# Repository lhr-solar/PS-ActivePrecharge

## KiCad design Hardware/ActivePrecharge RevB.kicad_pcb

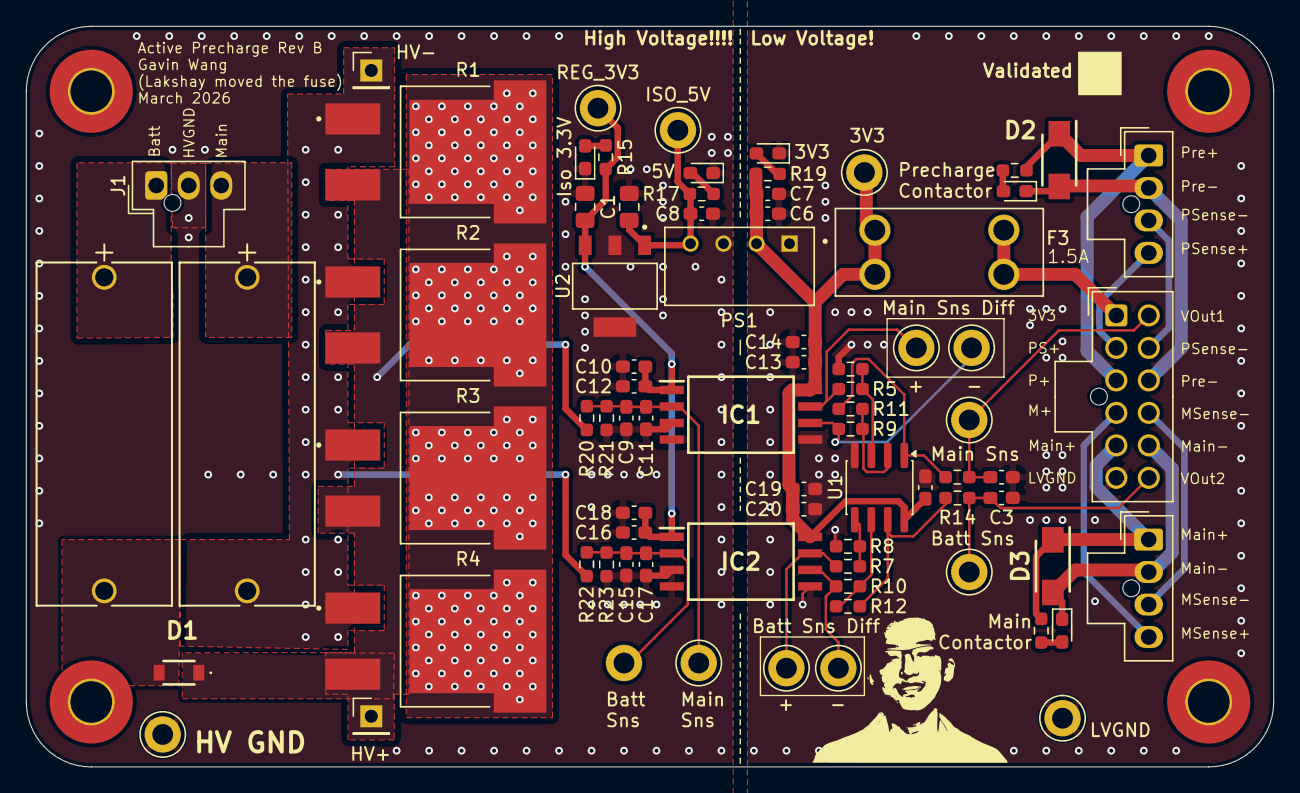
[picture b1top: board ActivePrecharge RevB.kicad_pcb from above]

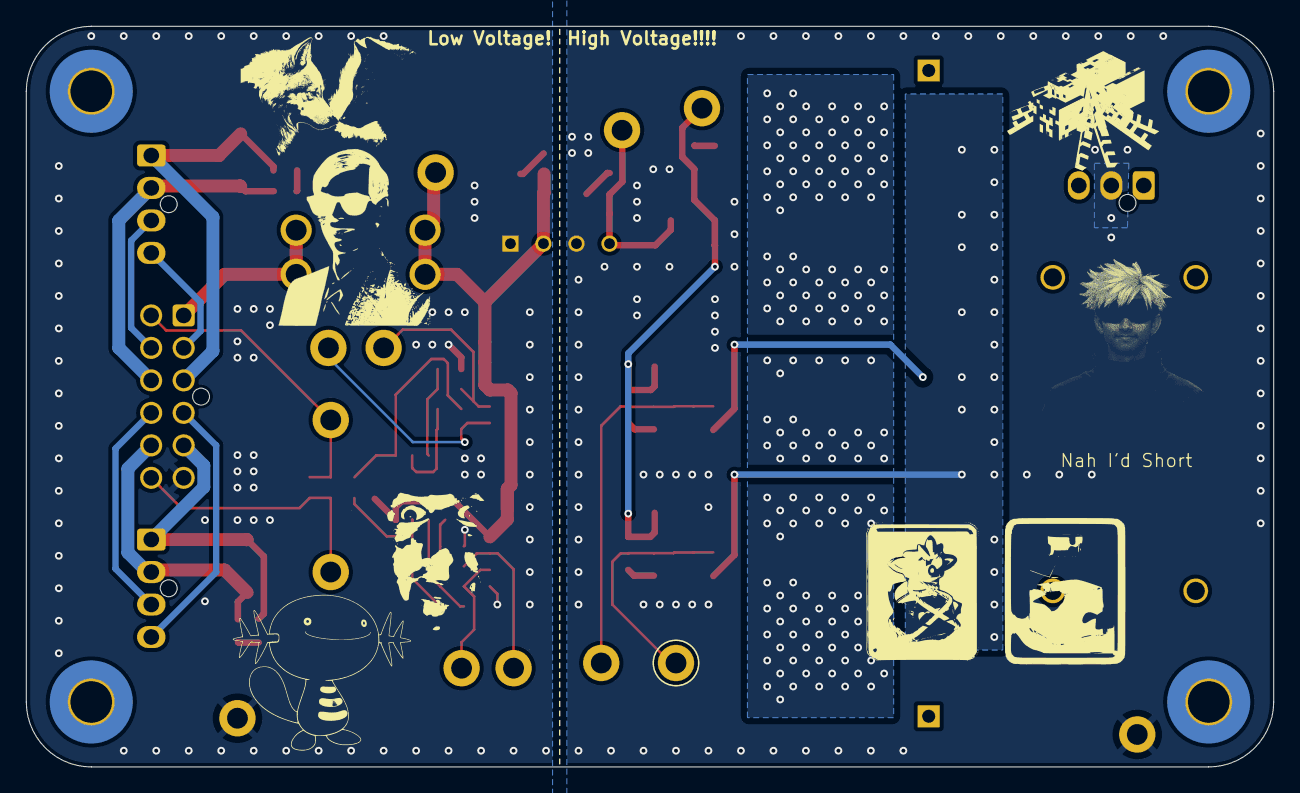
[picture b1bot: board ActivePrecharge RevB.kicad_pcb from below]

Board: 2 copper layers, 96.0 x 57.0 mm, 84 parts (2 on the bottom side), 39 nets.

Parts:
C1, C4: 10uF; C_0805_2012Metric_Pad1.18x1.45mm_HandSolder
C2, C3: 10nF; C_0603_1608Metric_Pad1.08x0.95mm_HandSolder
C5, C6, C7, C8, C9, C12, C13, C15, C18, C19: 1uF; C_0603_1608Metric_Pad1.08x0.95mm_HandSolder
C10, C14, C16, C20: 100nF; C_0603_1608Metric_Pad1.08x0.95mm_HandSolder
C11, C17: 1nF; C_0603_1608Metric_Pad1.08x0.95mm_HandSolder
D1: RSX068MP2STR
D2, D3: VSSAF522-M3/H; SODFL5026X125N
D4, D5, D6, D7, D8: LED; LED_0603_1608Metric_Pad1.05x0.95mm_HandSolder
F1, F2: 1.5A; HV-Fuse
F3: 1.5A; FUSE_3568
H1, H2, H3, H4: MountingHole_Pad; MountingHole_3.2mm_M3_Pad_TopBottom
IC1, IC2: AMC1350DWVR; SOIC127P1150X280-8N
J1: HVConnector; Molex_Nano-Fit_105309-xx03_1x03_P2.50mm_Vertical
J2: PrechargeContactor; Molex_Nano-Fit_105309-xx04_1x04_P2.50mm_Vertical
J3: MainContactor; Molex_Nano-Fit_105309-xx04_1x04_P2.50mm_Vertical
J4: ExportConnector; Molex_Nano-Fit_105310-xx12_2x06_P2.50mm_Vertical
J5: HV+; PinHeader_1x01_P2.54mm_Vertical
J6: HV-; PinHeader_1x01_P2.54mm_Vertical
LOGO1: Dr. Hallock; Hallock_Image_Tiny
LOGO2: Dr. Hallock; LHRs_LOGO
PS1: RM-3.305S; CONV_RM-3.305S
R1, R2, R3, R4: 330; RES_PWR263S-35-3300F
R5, R6, R7, R8, R9, R10, R11, R12, R16, R18: 10k; R_0603_1608Metric_Pad0.98x0.95mm_HandSolder
R13, R14: 10; R_0603_1608Metric_Pad0.98x0.95mm_HandSolder
R15, R17, R19: 1k; R_0603_1608Metric_Pad0.98x0.95mm_HandSolder
R20, R22: 100k; R_0603_1608Metric_Pad0.98x0.95mm_HandSolder
R21, R23: 2.49k; R_0603_1608Metric_Pad0.98x0.95mm_HandSolder
TP1: HVGND; TestPoint_Keystone_5005-5009_Compact
TP2: VOut1; TestPoint_Keystone_5005-5009_Compact
TP3: VOut2; TestPoint_Keystone_5005-5009_Compact
TP4: REG_3V3; TestPoint_Keystone_5005-5009_Compact
TP5: ISO_5V; TestPoint_Keystone_5005-5009_Compact
TP6, TP9: Vin; TestPoint_Keystone_5005-5009_Compact
TP7, TP10: V+; TestPoint_Keystone_5005-5009_Compact
TP8, TP11: V-; TestPoint_Keystone_5005-5009_Compact
TP12: 3v3; TestPoint_Keystone_5005-5009_Compact
TP13: GND; TestPoint_Keystone_5005-5009_Compact
U1: TLV9002QDRQ1; SOIC-8_3.9x4.9mm_P1.27mm
U2: LT1963AEST-3.3#TRPBF; VREG_LT1963AEST-3.3_TRPBF

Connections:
3V3: C5.1, C6.1, C7.1, C13.1, C14.1, C19.1, C20.1, F3.1, IC1.8 (VDD2), IC2.8 (VDD2), PS1.2 (+VIN), R19.1, TP12.1, U1.8 (V+)
/3V3_PreFuse: F3.2, J4.1
/HEAT_DISSIPATION: R1.3, R2.3, R3.3, R4.3
/HV+_Fused: D1.2 (A), F1.2
/HV+_PreFuse: F1.1, J1.1
/HV-_PreFuse: F2.1, J1.3
/Main+: D3.1 (K), J3.1 (Con+(24V)), J4.5, R18.1
/Main-: D3.2 (A), D7.1 (K), J3.2 (Con-), J4.11
/MainSense+: J3.4 (Sense+(24V)), J4.4
/MainSense-: J3.3 (Sense-), J4.10
/Pre+: D2.1 (K), J2.1 (Con+(24V)), J4.3, R16.1
/Pre-: D2.2 (A), D5.1 (K), J2.2 (Con-), J4.9
/PreSense+: J2.4 (Sense+(24V)), J4.2
/PreSense-: J2.3 (Sense-), J4.8
/V1+: IC1.7 (OUTP), R5.2, TP7.1
/V1-: IC1.6 (OUTN), R9.2, TP8.1
/V2+: IC2.7 (OUTP), R7.2, TP10.1
/V2-: IC2.6 (OUTN), R10.1, TP11.1
/VOut1: C2.1, J4.7, R13.1, TP2.1
/VOut2: C3.1, J4.12, R14.1, TP3.1
/Vin1: C9.1, C11.1, IC1.2 (INP), R20.1, R21.2, TP6.1
/Vin2: C15.1, C17.1, IC2.2 (INP), R22.1, R23.2, TP9.1
HV+: D1.1 (K), J5.1, R1.2, R2.2, R3.2, R4.2, R20.2
HV-: F2.2, J6.1, R1.1, R2.1, R3.1, R4.1, R22.2
HVGND: C1.2, C4.1, C8.1, C9.2, C10.2, C11.2, C12.2, C15.2, C16.2, C17.2, C18.2, D4.1 (K), D6.1 (K), IC1.3 (INN), IC1.4 (GND1), IC2.3 (INN), IC2.4 (GND1), J1.2, PS1.3 (-VOUT), R21.1, R23.1, TP1.1, U2.2 (GND), U2.4 (TAB)
ISO_5V: C1.1, C8.2, PS1.4 (+VOUT), R17.1, TP5.1, U2.1 (IN)
LVGND: C2.2, C3.2, C5.2, C6.2, C7.2, C13.2, C14.2, C19.2, C20.2, D8.1 (K), IC1.5 (GND2), IC2.5 (GND2), J4.6, PS1.1 (-VIN), R6.1, R8.1, TP13.1, U1.4 (V-)
unnamed: D4.2 (A), R15.2
unnamed: D5.2 (A), R16.2
unnamed: D6.2 (A), R17.2
unnamed: D7.2 (A), R18.2
unnamed: D8.2 (A), R19.2
unnamed: R11.1, R13.2, U1.1
unnamed: R12.2, R14.2, U1.7
unnamed: R5.1, R6.2, U1.3 (+)
unnamed: R9.1, R11.2, U1.2 (-)
unnamed: R7.1, R8.2, U1.5 (+)
unnamed: R10.2, R12.1, U1.6 (-)
REG_3V3: C4.2, C10.1, C12.1, C16.1, C18.1, IC1.1 (VDD1), IC2.1 (VDD1), R15.1, TP4.1, U2.3 (OUT)

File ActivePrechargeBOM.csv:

Qty,Value,P/N,Description
1,TLV9002QDRQ1,TLV9002QDRQ1,
3,1k,CRCW06031K00FKEI ,1k Resistor
2,1nF,MLASU063SB7102KFNA01,1nF Capacitor
10,1uF,MLASU168SB5105KTNA01,1uF Capacitors
3,1.5A,3568,1.5A Fuse
2,2.49k,CRCW06032K49FKEAC,2.49k Resistor
2,10,CRCW060310R0FKEE,10 Ohm Resistor
10,10k,CRCW060310K0FKEI,10k Resistor
2,10nF,MSASH168SB5103KTNA01,10nF Capacitor
2,10uF,GRM21BR61H106KE43K,10uF Capacitor
2,100k,CRCW0603100KFKEE,100k Resistor
4,100nF,MLASH168SB7104KTNA01,100nF Capacitor
1,RM-3.305S, RM-3.305S,3.3V to 5V DC/DC
1,LT1963AEST-3.3#TRPBF,LT1963AEST-3.3#TRPBF ,"3.3V, 1.5A, Low Noise, Fast Transient Response LDO Regulator, SOT-223"
2,VSSAF522-M3/H,VSSAF522-M3/H,Flyback diode
1,ExportConnector,1053101112,"Generic connector, double row, 02x06, counter clockwise pin numbering scheme (similar to DIP package numbering), script generated (kicad-library-utils/schlib/autogen/connector/)"
2,Conn_01x01_Pin,,"Generic connector, single row, 01x01, script generated"
1,Conn_01x02_Pin,,"Generic connector, single row, 01x02, script generated"
1,HVConnector,1053091103,"Generic connector, single row, 01x03, script generated (kicad-library-utils/schlib/autogen/connector/)"
2,AMC1350DWVR,AMC1350DWVR,Iso Opamps
5,LED,XL-1608UBC-06A,Light emitting diode
1,PrechargeContactor,1053091104,Pinout for contactor connectors.
1,MainContactor,1053091104,Pinout for contactor connectors.
3,330,  PWR263S-35-3300F,Precharge Resistor
1,330,  PWR263S-35-3300F,Precharge Resistor
1,RSX068MP2STR,RSX068MP2STR,Schottky diode

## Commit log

2025-09-22 Active Precharge Rev A
2025-09-23 Active Precharge Rev A with LDO and 3.3-5 ISO
2025-09-26 Active Precharge Rev A with comments addressed
2025-09-26 Active Precharge Rev A after Tony review
2025-09-27 With Ravi comments
2025-09-27 With footprints assigned
2025-09-30 Lakshay's comments addressed
2025-10-02 Lakshay's comments addressed, still need to move to new branch
2025-10-02 A few minor changes added bc i forgot some stuff
2025-10-03 Last changes addressed with organization changes and the new resolution implementation
2025-10-03 Adjustments made after Changxu examined the opamp circuit
2025-10-03 Added math for tolerancing on last opamp
2025-10-04 First Initial PCB Layout Finished
2025-10-11 All layout changes made except new symbol for precharge resistors for heat dissipation and new fuses
2025-10-11 All new comments addressed
2025-10-11 LVGND Stitching vias added to edges
2025-10-11 Part Numbers fleshed out
2025-10-11 Implemented all changes
2025-10-11 Renamed connector pins and added stitching vias for LVGND island
2025-10-11 Fixed pin, LED, and connector names being overwritten after updating PCB
2025-10-11 Deleted a redundant via on a thermal pad
2025-10-14 After nuking
2025-10-25 BOM generated
2025-10-25 BOM is actually inside the directory now
2025-11-08 Fixed 0.8V reference circuit short on accidental node for divider side
2025-12-19 Removed the 0.8V Reference circuit, changed the opamp, and changed the testpoints to make testing easier. Not sure how the connector is meant to be set up though
2025-12-26 Changed opamp to the TLV9002QDRQ1, separated the pin test points, changed 24V LED resitors to 10k (I don't remember what resistance you guys said), made 2 hierarchical sheets that are linked copies, 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
2025-12-27 Did some of the initial layout after schematic changes, concerned about the choking on how i currently have the opamp kind of set up, also havent touched the testpoints yet so that will probably make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
2026-01-02 First draft of the layout is complete, I think its workable rn but the vias might need a little work
2026-01-03 Addressed most things, still need to add more stitching vias, flybacks, change testpoints, and compact everything some more
2026-01-04 Made all layout changes. Ready for review. Also deleted some unnecessary files to clean up the libraries.
2026-01-08 Made all layout changes from last review, decreased precharge resistor pad vias, added more stitching vias, spaced testpoints furrther apart, added Active Precharge Rev B to the board, labeled tp is 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
2026-01-12 New branch after wipe
2026-01-12 submodules
2026-01-12 kicad sharept
2026-01-13 Fixed this shit finally im free
2026-01-13 fixed some testpoint silkscreen references i forgot about plus fixed 3d model embedding and added step file
2026-01-14 added some silkscreen stuff and gerbers + bom etc
2026-01-14 added some silkscreen stuff
2026-01-14 even MORE silkscreen stuff
2026-01-16 Rev B (#16)
    * New branch after wipe
    * Delete .DS_Store
    * submodules
    * kicad sharept
    * Fixed this shit finally im free
    * fixed some testpoint silkscreen references i forgot about plus fixed 3d model embedding and added step file
2026-03-15 changed fuses to be HV fuses
2026-03-15 add step file
2026-03-16 silk screen updates
2026-06-28 HV Fuse update (#18)
    * changed fuses to be HV fuses
    * add step file
    * silk screen updates
